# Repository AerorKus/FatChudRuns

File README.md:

# FatChudRuns
Threadmill for the crusty-ass white rat dog Tofu

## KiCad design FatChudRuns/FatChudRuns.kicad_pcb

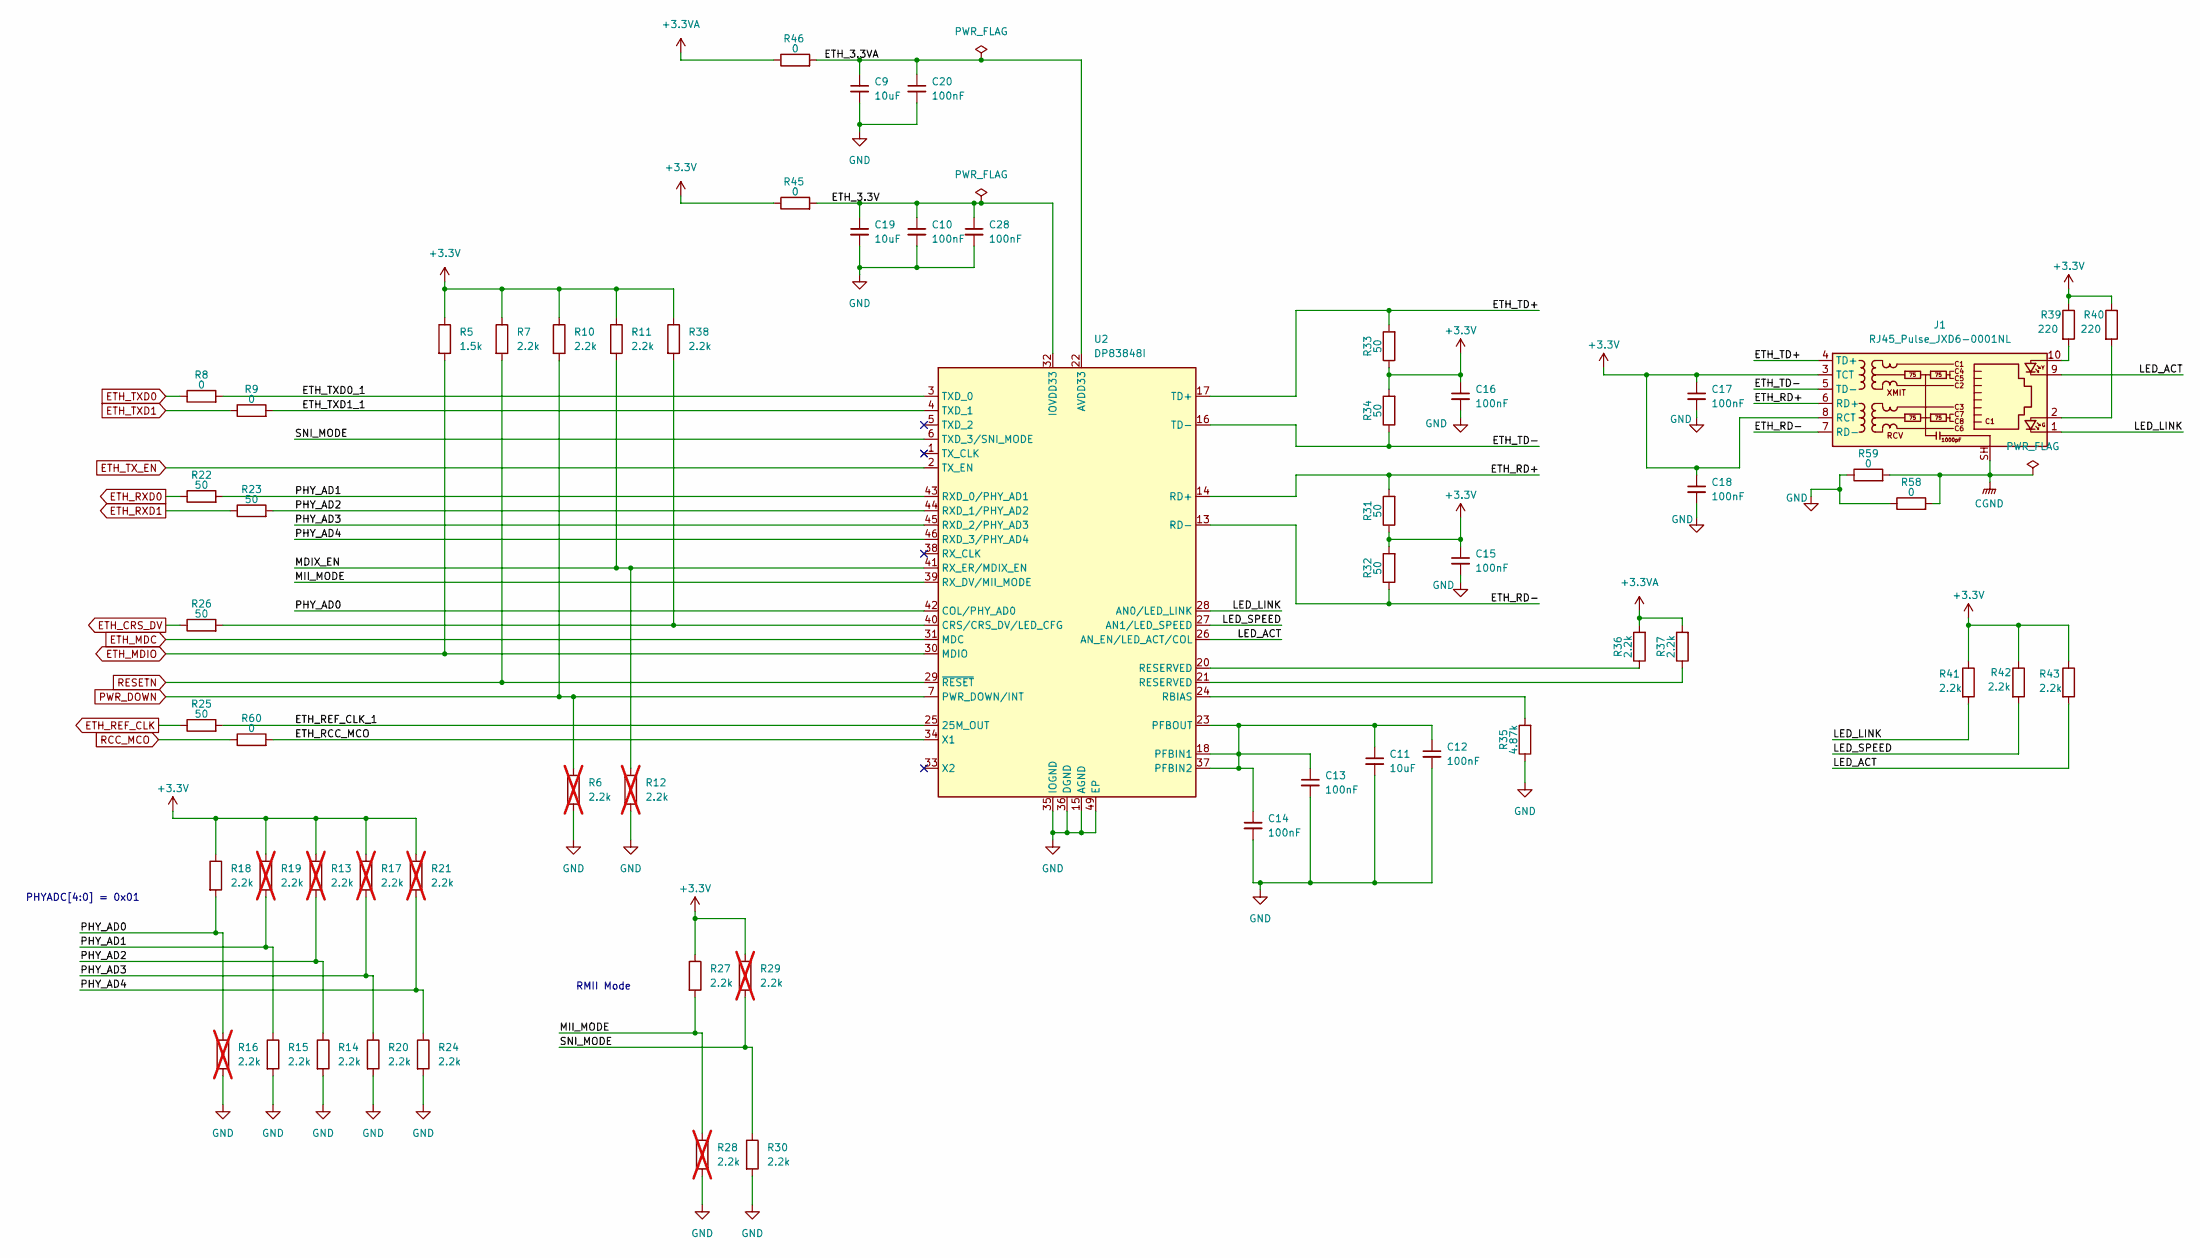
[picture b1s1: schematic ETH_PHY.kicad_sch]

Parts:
C9, C11, C19: 10uF; C_0805_2012Metric; JLCPCB Part # C2167271
C10, C12, C13, C14, C15, C16, C17, C18, C20, C28: 100nF; C_0603_1608Metric; JLCPCB Part # C2181816
J1: RJ45_Pulse_JXD6-0001NL; RJ45_Pulse_JXD6-0001NL_Horizontal; JLCPCB Part # C5359047
R5: 1.5k; R_0603_1608Metric; JLCPCB Part # C114668
R6, R12, R13, R16, R17, R19, R21, R28, R29: 2.2k; R_0603_1608Metric; not fitted
R7, R10, R11, R14, R15, R18, R20, R24, R27, R30, R36, R37, R38, R41, R42, R43: 2.2k; R_0603_1608Metric; JLCPCB Part # C113303
R8, R9, R45, R46, R58, R59, R60: 0; R_0603_1608Metric; JLCPCB Part # C95177
R22, R23, R25, R26, R31, R32, R33, R34: 50; R_0603_1608Metric; JLCPCB Part # C849792
R35: 4.87k; R_0603_1608Metric; JLCPCB Part # C137709
R39, R40: 220; R_0603_1608Metric; JLCPCB Part # C107696
U2: DP83848I; LQFP-48-1EP_7x7mm_P0.5mm_EP3.6x3.6mm_ThermalVias; JLCPCB Part # C12082

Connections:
+3.3V: C15.1, C16.1, C17.1, C18.1, J1.3 (TCT), J1.8 (RCT), R5.1, R7.1, R10.1, R11.1, R13.1, R17.1, R18.1, R19.1, R21.1, R27.1, R29.1, R31.1, R32.2, R33.1, R34.2, R38.1, R39.1, R40.1, R41.1, R42.1, R43.1, R45.1; also elsewhere on the board
+3.3VA: R36.2, R37.2, R46.1; also elsewhere on the board
/ETH_PHY/ETH_3.3V: C10.1, C19.1, C28.1, R45.2, U2.32 (IOVDD33), U2.48 (IOVDD33)
/ETH_PHY/ETH_3.3VA: C9.1, C20.1, R46.2, U2.22 (AVDD33)
/ETH_PHY/ETH_RCC_MCO: R60.2, U2.34 (X1)
/ETH_PHY/ETH_RD+: J1.6 (RD+), R31.2, U2.14 (RD+)
/ETH_PHY/ETH_RD-: J1.7 (RD-), R32.1, U2.13 (RD-)
/ETH_PHY/ETH_REF_CLK_1: R25.2, U2.25 (25M_OUT)
/ETH_PHY/ETH_TD+: J1.4 (TD+), R33.2, U2.17 (TD+)
/ETH_PHY/ETH_TD-: J1.5 (TD-), R34.1, U2.16 (TD-)
/ETH_PHY/ETH_TXD0_1: R8.2, U2.3 (TXD_0)
/ETH_PHY/ETH_TXD1_1: R9.2, U2.4 (TXD_1)
/ETH_PHY/LED_ACT: J1.9, R43.2, U2.26 (AN_EN/LED_ACT/COL)
/ETH_PHY/LED_LINK: J1.1, R41.2, U2.28 (AN0/LED_LINK)
/ETH_PHY/LED_SPEED: R42.2, U2.27 (AN1/LED_SPEED)
/ETH_PHY/MDIX_EN: R11.2, R12.1, U2.41 (RX_ER/MDIX_EN)
/ETH_PHY/MII_MODE: R27.2, R28.1, U2.39 (RX_DV/MII_MODE)
/ETH_PHY/PHY_AD0: R16.1, R18.2, U2.42 (COL/PHY_AD0)
/ETH_PHY/PHY_AD1: R15.1, R19.2, R22.2, U2.43 (RXD_0/PHY_AD1)
/ETH_PHY/PHY_AD2: R13.2, R14.1, R23.2, U2.44 (RXD_1/PHY_AD2)
/ETH_PHY/PHY_AD3: R17.2, R20.1, U2.45 (RXD_2/PHY_AD3)
/ETH_PHY/PHY_AD4: R21.2, R24.1, U2.46 (RXD_3/PHY_AD4)
/ETH_PHY/SNI_MODE: R29.2, R30.1, U2.6 (TXD_3/SNI_MODE)
CGND: J1.SH, R58.2, R59.2
ETH_CRS_DV: R26.1; also elsewhere on the board
ETH_MDC: U2.31 (MDC); also elsewhere on the board
ETH_MDIO: R5.2, U2.30 (MDIO); also elsewhere on the board
ETH_REF_CLK: R25.1; also elsewhere on the board
ETH_RXD0: R22.1; also elsewhere on the board
ETH_RXD1: R23.1; also elsewhere on the board
ETH_TXD0: R8.1; also elsewhere on the board
ETH_TXD1: R9.1; also elsewhere on the board
ETH_TX_EN: U2.2 (TX_EN); also elsewhere on the board
GND: C9.2, C10.2, C11.2, C12.2, C13.2, C14.2, C15.2, C16.2, C17.2, C18.2, C19.2, C20.2, C28.2, R6.2, R12.2, R14.2, R15.2, R16.2, R20.2, R24.2, R28.2, R30.2, R35.1, R58.1, R59.1, U2.15 (AGND), U2.19 (AGND), U2.35 (IOGND), U2.36 (DGND), U2.47 (IOGND), U2.49 (EP); also elsewhere on the board
unnamed: J1.2, R40.2
unnamed: J1.10, R39.2
unnamed: R36.1, U2.20 (RESERVED)
unnamed: R37.1, U2.21 (RESERVED)
unnamed: R26.2, R38.2, U2.40 (CRS/CRS_DV/LED_CFG)
unnamed: C11.1, C12.1, C13.1, C14.1, U2.18 (PFBIN1), U2.23 (PFBOUT), U2.37 (PFBIN2)
unnamed: R35.2, U2.24 (RBIAS)
PWR_DOWN: R6.1, R10.2, U2.7 (PWR_DOWN/INT)
RCC_MCO: R60.1; also elsewhere on the board
RESETN: R7.2, U2.29 (~RESET)

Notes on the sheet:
RMII Mode
PHYADC[4:0] = 0x01

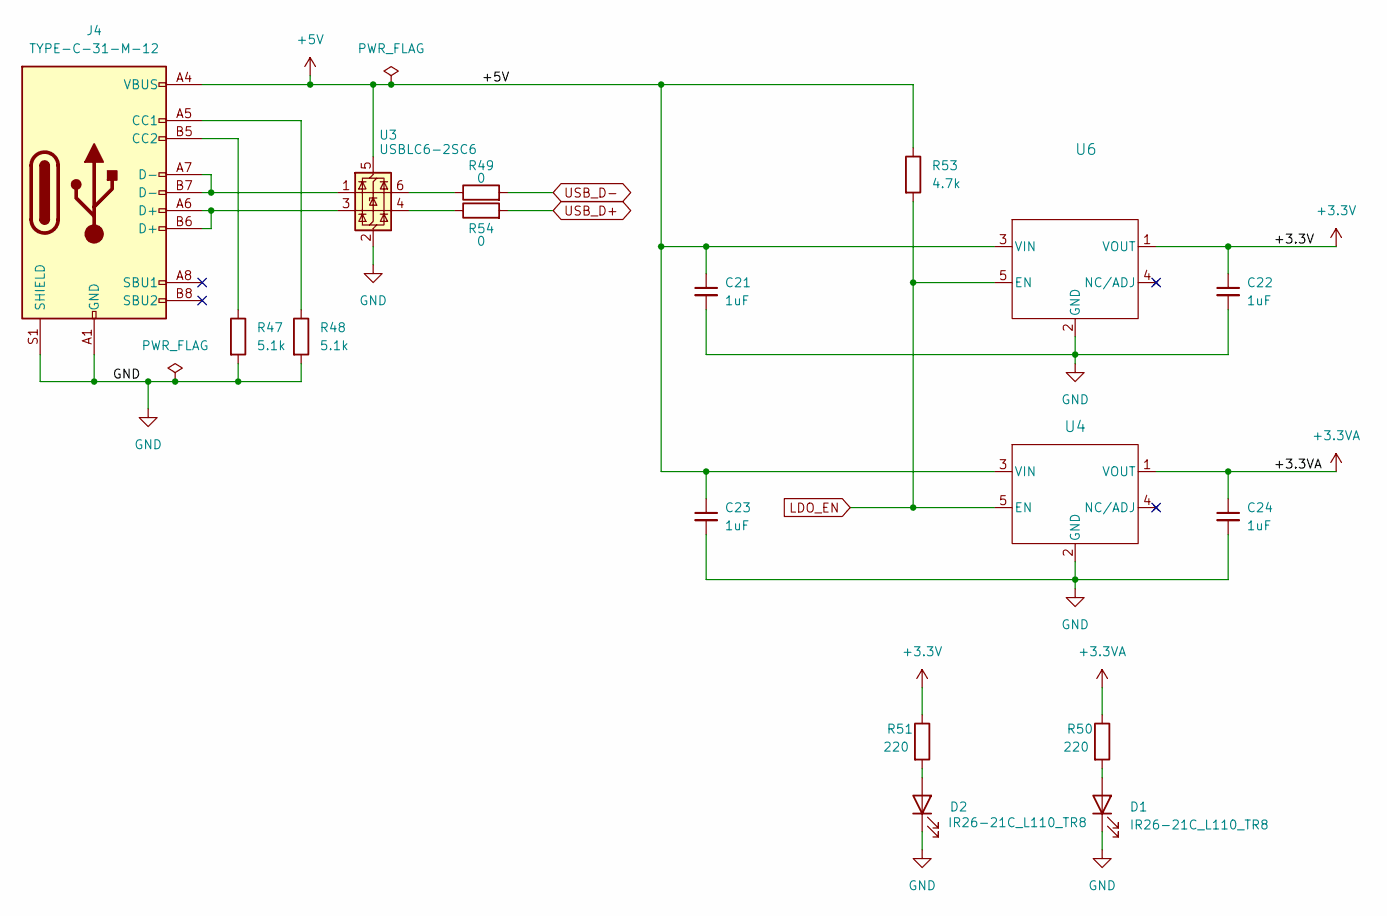
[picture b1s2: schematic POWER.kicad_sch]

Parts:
C21, C22, C23, C24: 1uF; C_0603_1608Metric; JLCPCB Part # C561804
D1, D2: IR26-21C_L110_TR8; LED_1206_3216Metric; JLCPCB Part # C73929
J4: TYPE-C-31-M-12; USB_C_Receptacle_GCT_USB4105-xx-A_16P_TopMnt_Horizontal; JLCPCB Part # C165948
R47, R48: 5.1k; R_0603_1608Metric; JLCPCB Part # C14677
R49, R54: 0; R_0603_1608Metric; JLCPCB Part # C95177
R50, R51: 220; R_0603_1608Metric; JLCPCB Part # C107696
R53: 4.7k; R_0603_1608Metric; JLCPCB Part # C99782
U3: USBLC6-2SC6; SOT-23-6; JLCPCB Part # C7519
U4, U6: ST730M33R; SOT_30M33R_STM; JLCPCB Part # C2846046

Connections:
+3.3V: C22.1, R51.1, U6.1 (VOUT); also elsewhere on the board
+3.3VA: C24.1, R50.1, U4.1 (VOUT); also elsewhere on the board
+5V: C21.1, C23.1, J4.A4 (VBUS), J4.A9 (VBUS), J4.B4 (VBUS), J4.B9 (VBUS), R53.1, U3.5 (VBUS), U4.3 (VIN), U6.3 (VIN)
GND: C21.2, C22.2, C23.2, C24.2, D1.1 (K), D2.1 (K), J4.A1 (GND), J4.A12 (GND), J4.B1 (GND), J4.B12 (GND), J4.S1 (SHIELD), R47.2, R48.2, U3.2 (GND), U4.2 (GND), U6.2 (GND); also elsewhere on the board
LDO_EN: R53.2, U4.5 (EN), U6.5 (EN); also elsewhere on the board
unnamed: D1.2 (A), R50.2
unnamed: D2.2 (A), R51.2
unnamed: J4.A5 (CC1), R48.1
unnamed: J4.B5 (CC2), R47.1
unnamed: J4.A6 (D+), J4.B6 (D+), U3.3 (I/O2)
unnamed: J4.A7 (D-), J4.B7 (D-), U3.1 (I/O1)
unnamed: R49.1, U3.6 (I/O1)
unnamed: R54.1, U3.4 (I/O2)
USB_D+: R54.2; also elsewhere on the board
USB_D-: R49.2; also elsewhere on the board

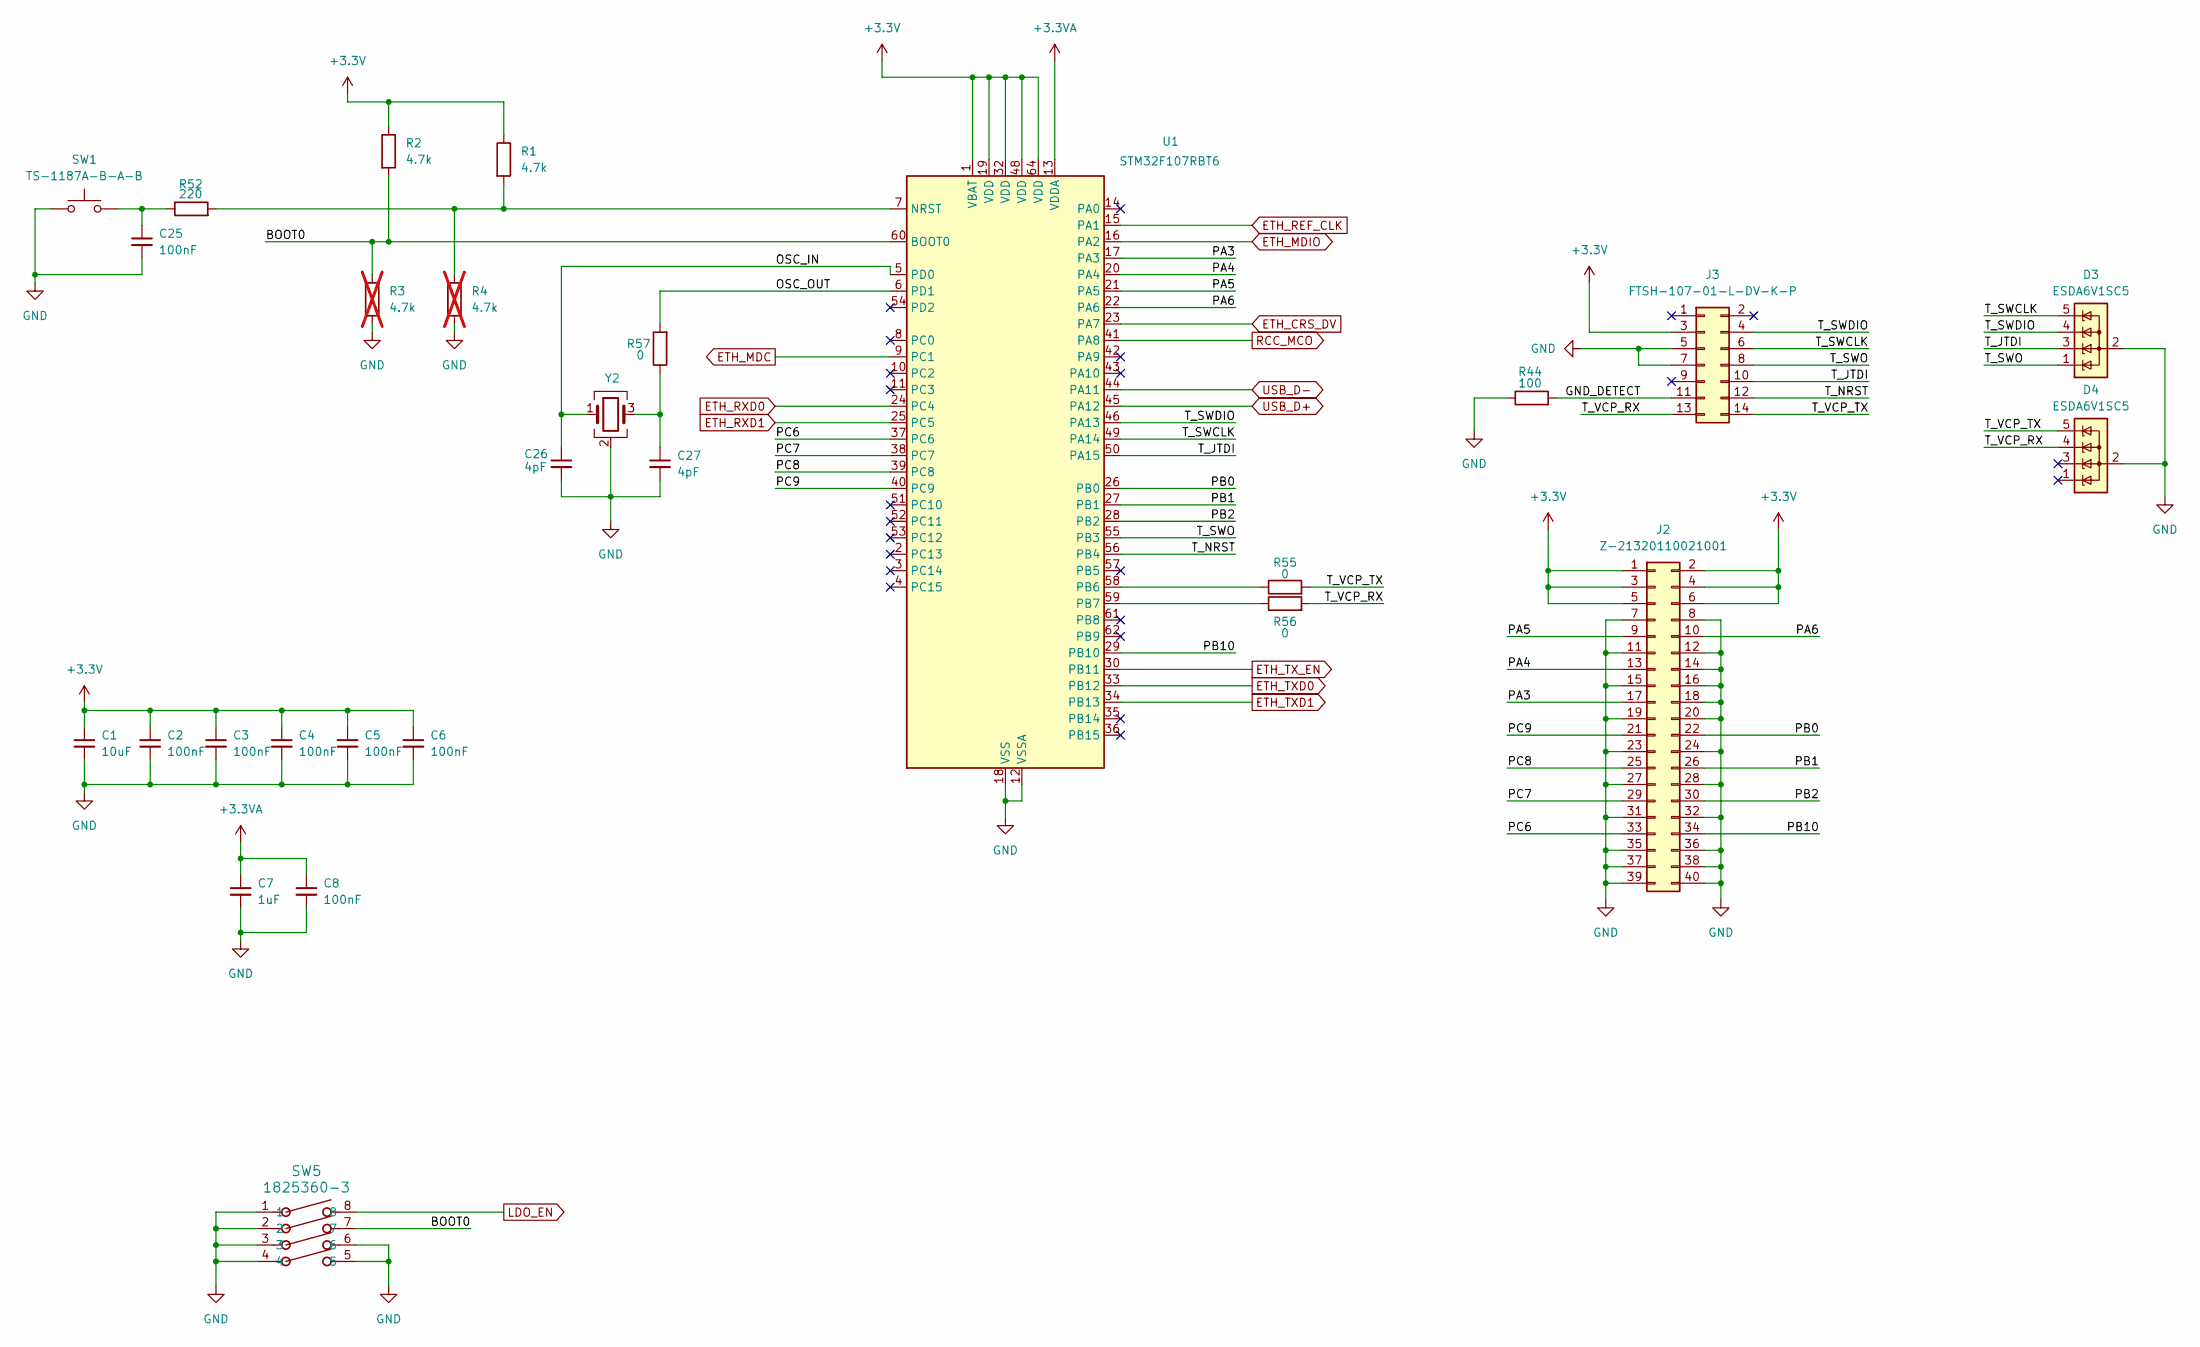
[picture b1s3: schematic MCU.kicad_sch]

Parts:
C1: 10uF; C_0805_2012Metric; JLCPCB Part # C2167271
C2, C3, C4, C5, C6, C8, C25: 100nF; C_0603_1608Metric; JLCPCB Part # C2181816
C7: 1uF; C_0603_1608Metric; JLCPCB Part # C561804
C26, C27: 4pF; C_0603_1608Metric; JLCPCB Part # C309461
D3, D4: ESDA6V1SC5; SOT-23-5; JLCPCB Part # C2935146
J2: Z-21320110021001; PinSocket_2x20_P2.54mm_Vertical; JLCPCB Part # C193453
J3: FTSH-107-01-L-DV-K-P; CON14_2X7_DUK_FTSH_SAI; JLCPCB Part # C5345538
R1, R2: 4.7k; R_0603_1608Metric; JLCPCB Part # C99782
R3, R4: 4.7k; R_0603_1608Metric; not fitted
R44: 100; R_0603_1608Metric; JLCPCB Part # C105588
R52: 220; R_0603_1608Metric; JLCPCB Part # C107696
R55, R56, R57: 0; R_0603_1608Metric; JLCPCB Part # C95177
SW1: TS-1187A-B-A-B; SW_SPST_TL3342; JLCPCB Part # C318884
SW5: 1825360-3; SWDIP8_300X185P100; JLCPCB Part # C574798
U1: STM32F107RBT6; LQFP-64_10x10mm_P0.5mm; JLCPCB Part # C16918
Y2: ABM8G-25.000MHZ-B4Y-T; Crystal_SMD_Abracon_ABM8AIG-4Pin_3.2x2.5mm; JLCPCB Part # C596913

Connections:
+3.3V: C1.1, C2.1, C3.1, C4.1, C5.1, C6.1, J2.1, J2.2, J2.3, J2.4, J2.5, J2.6, J3.3, R1.1, R2.1, U1.1 (VBAT), U1.19 (VDD), U1.32 (VDD), U1.48 (VDD), U1.64 (VDD); also elsewhere on the board
+3.3VA: C7.1, C8.1, U1.13 (VDDA); also elsewhere on the board
/MCU/BOOT0: R2.2, R3.1, SW5.7, U1.60 (BOOT0)
/MCU/GND_DETECT: J3.11, R44.2
/MCU/OSC_IN: C26.1, U1.5 (PD0), Y2.1
/MCU/OSC_OUT: R57.2, U1.6 (PD1)
/MCU/PA3: J2.17, U1.17 (PA3)
/MCU/PA4: J2.13, U1.20 (PA4)
/MCU/PA5: J2.9, U1.21 (PA5)
/MCU/PA6: J2.10, U1.22 (PA6)
/MCU/PB0: J2.22, U1.26 (PB0)
/MCU/PB1: J2.26, U1.27 (PB1)
/MCU/PB2: J2.30, U1.28 (PB2)
/MCU/PB10: J2.34, U1.29 (PB10)
/MCU/PC6: J2.33, U1.37 (PC6)
/MCU/PC7: J2.29, U1.38 (PC7)
/MCU/PC8: J2.25, U1.39 (PC8)
/MCU/PC9: J2.21, U1.40 (PC9)
/MCU/T_JTDI: D3.3 (K), J3.10, U1.50 (PA15)
/MCU/T_NRST: J3.12, U1.56 (PB4)
/MCU/T_SWCLK: D3.5 (K), J3.6, U1.49 (PA14)
/MCU/T_SWDIO: D3.4 (K), J3.4, U1.46 (PA13)
/MCU/T_SWO: D3.1 (K), J3.8, U1.55 (PB3)
/MCU/T_VCP_RX: D4.4 (K), J3.13, R56.2
/MCU/T_VCP_TX: D4.5 (K), J3.14, R55.2
ETH_CRS_DV: U1.23 (PA7); also elsewhere on the board
ETH_MDC: U1.9 (PC1); also elsewhere on the board
ETH_MDIO: U1.16 (PA2); also elsewhere on the board
ETH_REF_CLK: U1.15 (PA1); also elsewhere on the board
ETH_RXD0: U1.24 (PC4); also elsewhere on the board
ETH_RXD1: U1.25 (PC5); also elsewhere on the board
ETH_TXD0: U1.33 (PB12); also elsewhere on the board
ETH_TXD1: U1.34 (PB13); also elsewhere on the board
ETH_TX_EN: U1.30 (PB11); also elsewhere on the board
GND: C1.2, C2.2, C3.2, C4.2, C5.2, C6.2, C7.2, C8.2, C25.2, C26.2, C27.2, D3.2 (A), D4.2 (A), J2.7, J2.8, J2.11, J2.12, J2.14, J2.15, J2.16, J2.18, J2.19, J2.20, J2.23, J2.24, J2.27, J2.28, J2.31, J2.32, J2.35, J2.36, J2.37, J2.38, J2.39, J2.40, J3.5, J3.7, R3.2, R4.2, R44.1, SW1.1, SW5.1, SW5.2, SW5.3, SW5.4, SW5.5, SW5.6, U1.12 (VSSA), U1.18 (VSS), U1.31 (VSS), U1.47 (VSS), U1.63 (VSS), Y2.2 (G), Y2.4 (G); also elsewhere on the board
LDO_EN: SW5.8; also elsewhere on the board
unnamed: C25.1, R52.1, SW1.2
unnamed: C27.1, R57.1, Y2.3
unnamed: R1.2, R4.1, R52.2, U1.7 (NRST)
unnamed: R55.1, U1.58 (PB6)
unnamed: R56.1, U1.59 (PB7)
RCC_MCO: U1.41 (PA8); also elsewhere on the board
USB_D+: U1.45 (PA12); also elsewhere on the board
USB_D-: U1.44 (PA11); also elsewhere on the board

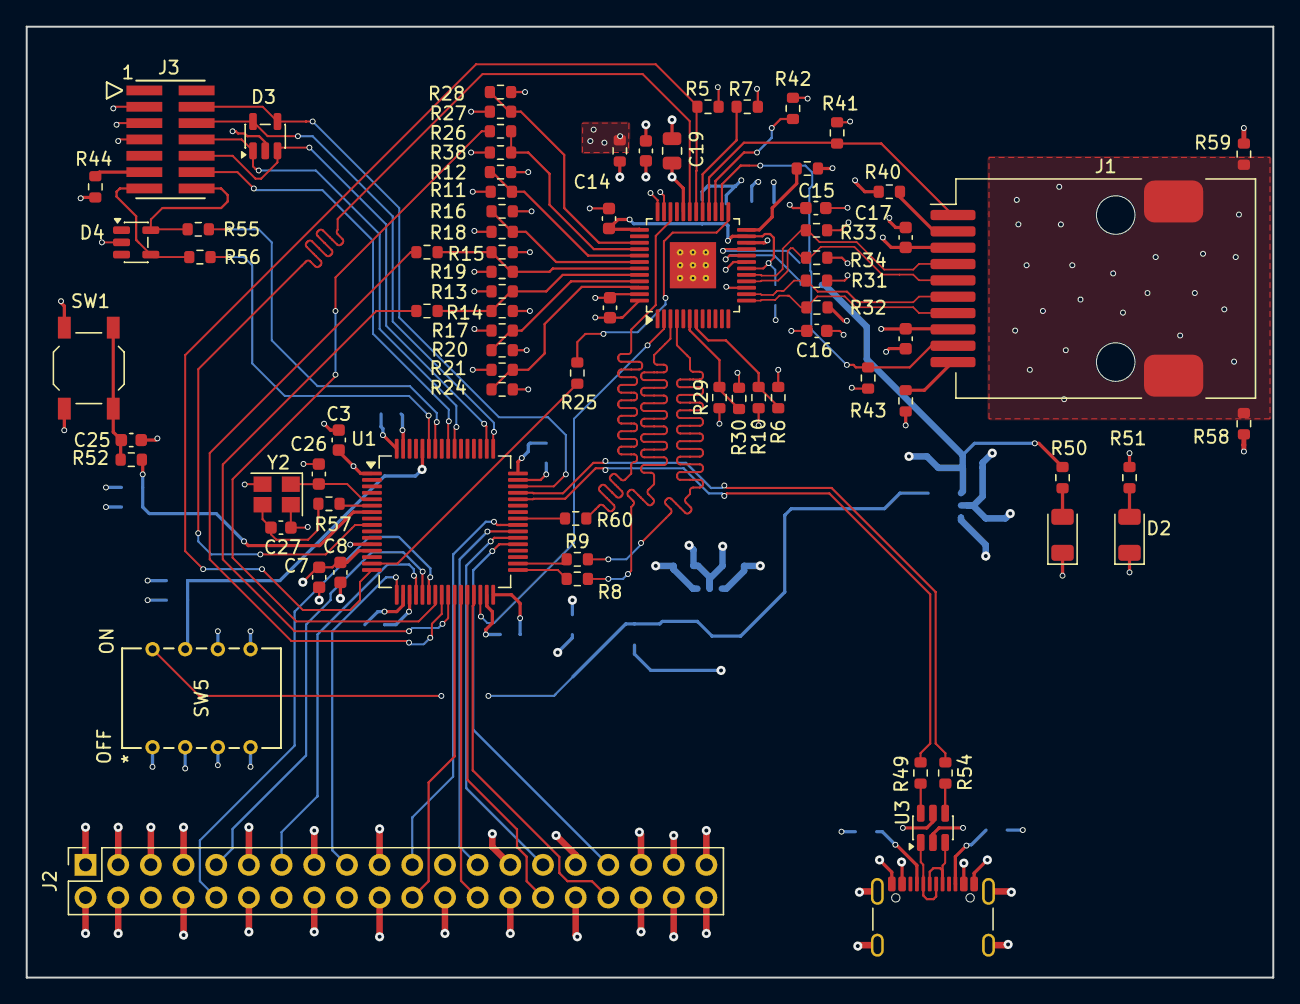
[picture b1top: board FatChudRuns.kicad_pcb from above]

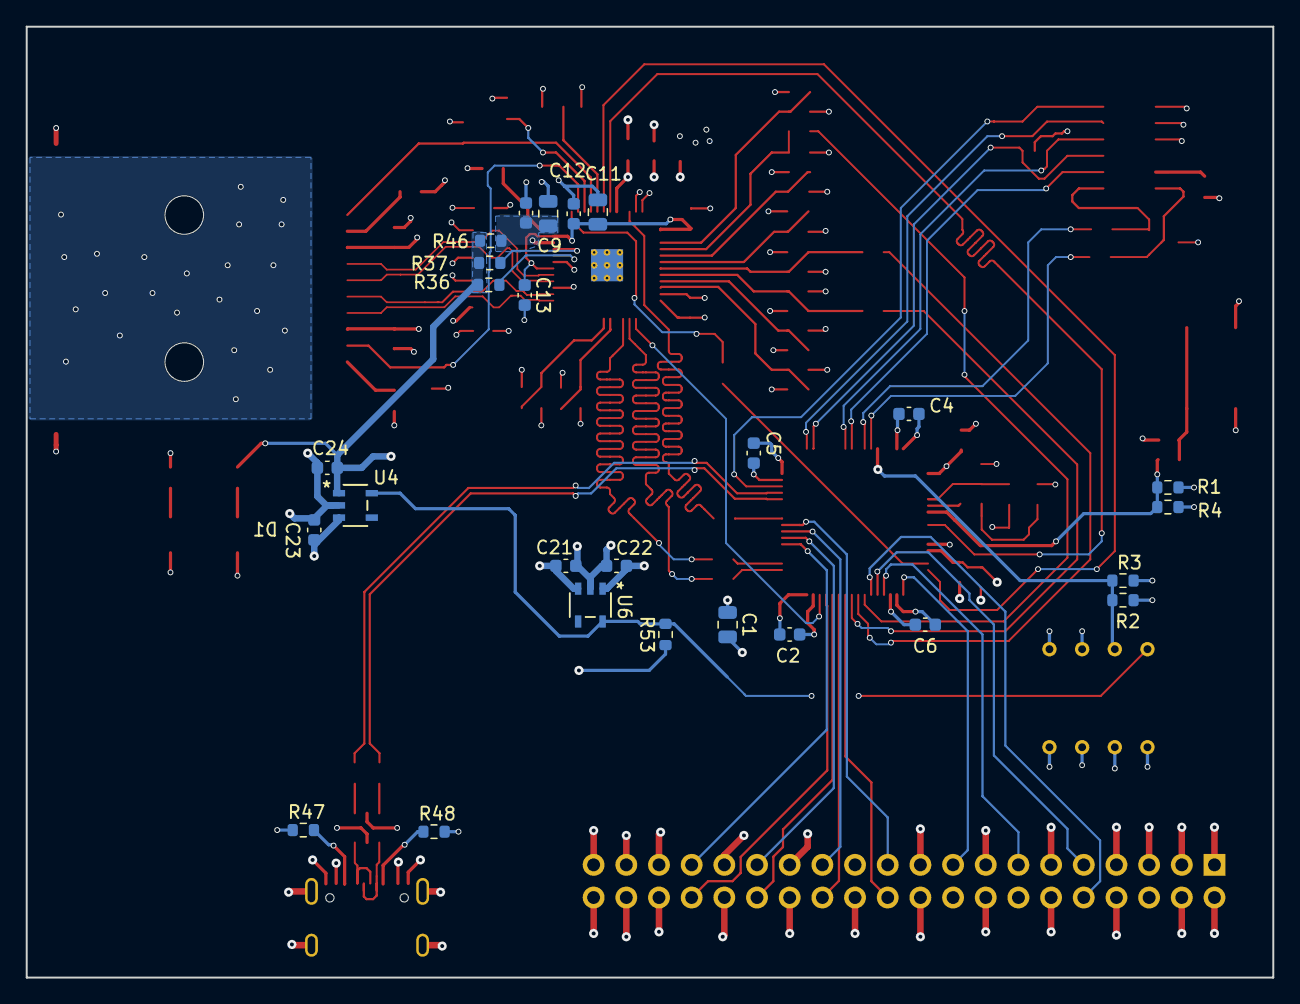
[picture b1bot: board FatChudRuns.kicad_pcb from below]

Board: 4 copper layers, 96.9 x 73.9 mm, 104 parts (26 on the bottom side), 84 nets.

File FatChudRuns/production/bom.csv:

Designator,Footprint,Quantity,Value,LCSC Part #
"C1, C11, C19, C9",0805,4,10uF,C2167271
"C10, C12, C13, C14, C15, C16, C17, C18, C2, C20, C25, C28, C3, C4, C5, C6, C8",0603,17,100nF,C2181816
"C21, C22, C23, C24, C7",0603,5,1uF,C561804
"C26, C27",0603,2,4pF,C309461
"D1, D2",1206,2,IR26-21C_L110_TR8,C73929
"D3, D4",SOT-23-5,2,ESDA6V1SC5,C2935146
J1,RJ45_Pulse_JXD6-0001NL_Horizontal,1,RJ45_Pulse_JXD6-0001NL,C5359047
J2,PinSocket_2x20_P2.54mm_Vertical,1,2.54mm 2*20P直排针,C50980
J3,CON14_2X7_DUK_FTSH_SAI,1,FTSH-107-01-L-DV-K-P,C5345538
J4,USB_C_Receptacle_GCT_USB4105-xx-A_16P_TopMnt_Horizontal,1,TYPE-C-31-M-12,C165948
"R1, R2, R53",0603,3,4.7k,C99782
"R10, R11, R14, R15, R18, R20, R24, R27, R30, R36, R37, R38, R41, R42, R43, R7",0603,16,2.2k,C113303
"R22, R23, R25, R26, R31, R32, R33, R34",0603,8,50,C849792
R35,0603,1,4.87k,C137709
"R39, R40, R50, R51, R52",0603,5,220,C107696
R44,0603,1,100,C105588
"R45, R46, R49, R54, R55, R56, R57, R58, R59, R60, R8, R9",0603,12,0,C95177
"R47, R48",0603,2,5.1k,C14677
R5,0603,1,1.5k,C114668
SW1,SW_SPST_TL3342,1,TS-1187A-B-A-B,C318884
SW5,SWDIP8_300X185P100,1,1825360-3,C574798
U1,LQFP-64_10x10mm_P0.5mm,1,STM32F107RBT6,C16918
U2,LQFP-48-1EP_7x7mm_P0.5mm_EP3.6x3.6mm_ThermalVias,1,DP83848I,C12082
U3,SOT-23-6,1,USBLC6-2SC6,C7519
"U4, U6",SOT_30M33R_STM,2,ST730M33R,C2846046
Y2,Crystal_SMD_Abracon_ABM8AIG-4Pin_3.2x2.5mm,1,ABM8G-25.000MHZ-B4Y-T,C596913

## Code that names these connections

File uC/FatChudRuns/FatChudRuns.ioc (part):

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Mcu.Name=STM32F107R(B-C)Tx
Mcu.Package=LQFP64
Mcu.UserName=STM32F107RBTx
PA1.Mode=RMII
PA1.Signal=ETH_REF_CLK
PA10.Mode=Asynchronous
PA10.Signal=USART1_RX
PA11.Mode=Device_Only
PA11.Signal=USB_OTG_FS_DM
PA12.Mode=Device_Only
PA12.Signal=USB_OTG_FS_DP
PA13.Mode=JTAG_5_pins
PA13.Signal=SYS_JTMS-SWDIO
PA14.Mode=JTAG_5_pins
PA14.Signal=SYS_JTCK-SWCLK
PA15.Mode=JTAG_5_pins
PA15.Signal=SYS_JTDI
PA2.Mode=RMII
PA2.Signal=ETH_MDIO
PA7.Mode=RMII
PA7.Signal=ETH_CRS_DV
PA8.Mode=Clock-out
PA8.Signal=RCC_MCO
PA9.Mode=Asynchronous
PA9.Signal=USART1_TX
PB11.Mode=RMII
PB11.Signal=ETH_TX_EN
PB12.Mode=RMII
PB12.Signal=ETH_TXD0
PB13.Mode=RMII
PB13.Signal=ETH_TXD1
PB3.Mode=JTAG_5_pins
PB3.Signal=SYS_JTDO
PB4.Mode=JTAG_5_pins
PB4.Signal=SYS_NJTRST
PC1.Mode=RMII
PC1.Signal=ETH_MDC
PC4.Mode=RMII
PC4.Signal=ETH_RXD0
PC5.Mode=RMII
PC5.Signal=ETH_RXD1
PC6.Signal=S_TIM3_CH1
PC7.Signal=S_TIM3_CH2
PC8.Signal=S_TIM3_CH3
PC9.Signal=S_TIM3_CH4
PD0-OSC_IN.Mode=HSE-External-Oscillator
PD0-OSC_IN.Signal=RCC_OSC_IN
PD1-OSC_OUT.Mode=HSE-External-Oscillator
PD1-OSC_OUT.Signal=RCC_OSC_OUT
RCC.HSEDivPLL=RCC_HSE_PREDIV_DIV5
RCC.HSE_VALUE=25000000
RCC.SYSCLKFreq_VALUE=72000000
RCC.SYSCLKSource=RCC_SYSCLKSOURCE_PLLCLK
board=custom

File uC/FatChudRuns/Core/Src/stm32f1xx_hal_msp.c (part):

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    __HAL_RCC_GPIOA_CLK_ENABLE();
    /**ADC2 GPIO Configuration
    PA0-WKUP     ------> ADC2_IN0
    PA3     ------> ADC2_IN3
    */
    GPIO_InitStruct.Pin = GPIO_PIN_0|GPIO_PIN_3;
    GPIO_InitStruct.Mode = GPIO_MODE_ANALOG;
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
    /**ADC2 GPIO Configuration
    PA0-WKUP     ------> ADC2_IN0
    PA3     ------> ADC2_IN3
    */
    HAL_GPIO_DeInit(GPIOA, GPIO_PIN_0|GPIO_PIN_3);

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
    __HAL_RCC_GPIOA_CLK_ENABLE();
    /**DAC GPIO Configuration
    PA4     ------> DAC_OUT1
    PA5     ------> DAC_OUT2
    */
    GPIO_InitStruct.Pin = GPIO_PIN_4|GPIO_PIN_5;
    GPIO_InitStruct.Mode = GPIO_MODE_ANALOG;
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    __HAL_RCC_DAC_CLK_DISABLE();

    /**DAC GPIO Configuration
    PA4     ------> DAC_OUT1
    PA5     ------> DAC_OUT2
    */
    HAL_GPIO_DeInit(GPIOA, GPIO_PIN_4|GPIO_PIN_5);

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    __HAL_RCC_GPIOA_CLK_ENABLE();
    __HAL_RCC_GPIOB_CLK_ENABLE();
    /**ETH GPIO Configuration
    PC1     ------> ETH_MDC
    PA1     ------> ETH_REF_CLK
    PA2     ------> ETH_MDIO
    PA7     ------> ETH_CRS_DV
    PC4     ------> ETH_RXD0
    PC5     ------> ETH_RXD1
    PB11     ------> ETH_TX_EN
    PB12     ------> ETH_TXD0
    PB13     ------> ETH_TXD1
    */
    GPIO_InitStruct.Pin = GPIO_PIN_1;
    GPIO_InitStruct.Mode = GPIO_MODE_AF_PP;
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    __HAL_RCC_ETH_CLK_DISABLE();

    /**ETH GPIO Configuration
    PC1     ------> ETH_MDC
    PA1     ------> ETH_REF_CLK
    PA2     ------> ETH_MDIO
    PA7     ------> ETH_CRS_DV
    PC4     ------> ETH_RXD0
    PC5     ------> ETH_RXD1
    PB11     ------> ETH_TX_EN
    PB12     ------> ETH_TXD0
    PB13     ------> ETH_TXD1
    */
    HAL_GPIO_DeInit(GPIOC, GPIO_PIN_1|GPIO_PIN_4|GPIO_PIN_5);

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
    __HAL_RCC_GPIOB_CLK_ENABLE();
    /**TIM3 GPIO Configuration
    PB0     ------> TIM3_CH3
    PB1     ------> TIM3_CH4
    PB4     ------> TIM3_CH1
    PB5     ------> TIM3_CH2
    */
    GPIO_InitStruct.Pin = GPIO_PIN_0|GPIO_PIN_1|GPIO_PIN_4|GPIO_PIN_5;
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
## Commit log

2026-02-07 updated stm32 firmware for pin selection, added pcb guidelines pdf
2026-02-10 added switch and dip switch for mcu, decoup caps. new sheets for power and eth phy
2026-02-11 connected phy to uC and added strapping options
2026-02-12 added filters and decoup caps, updated series term
2026-02-19 selected rj45 w/ mag, fixed filtering for power, added snippets of layout recs
2026-02-23 connected rj45 and leds and led strapping resistors
2026-03-01 added connectors for gpio and jtag, need to verify orientation
2026-03-02 added debugger and nucleo ref sch
2026-03-03 connected remaining gpio pins to connector, added kicad power pins instead of net names
2026-03-04 add usb c power circuitry, added led for power indication, increased resistance of ethernet leds light to 220ohms
2026-03-04 cleaned up ref folder, added ldo datasheet
2026-03-07 sorted out erc errors and warning, connected tvs diodes to jtag
2026-03-09 added caps and diode footprints, all caps now non-polarized ceramic caps
2026-03-14 added footprint for switches and button - ready for layout
2026-03-20 setup stackup and constraints
2026-03-22 added 4pF caps and Rext to XTAL, initial placement of PCB, added board outline and gnd plane
2026-03-23 routed ETH MDI and magnetics portion with chassis ground. added 0ohm resistors to connect gnd and cgnd
2026-03-24 added one more decoup cap for eth phy (another power pin), routed decoup caps, routed phy filter resistors
2026-03-29 routed phy usb and clock
2026-03-31 routed jtag, ldo, switch, reset button, and decoupling caps. only need GPIO signals
2026-04-01 finished initial layout, removed some gpio pins and reorganized them
2026-04-01 updated constraints, parsed through most drc
2026-04-03 cleared the rest of the drc - layout complete
2026-04-03 created gerbers, need to fix dfm
2026-04-10 updated 3d model footprint for Rj45 (created new library)
2026-04-10 updated 10uF to 0805, completed BOM, sent to fab

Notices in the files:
uC/FatChudRuns/Core/Src/stm32f1xx_hal_msp.c:
Copyright (c) 2026 STMicroelectronics.
All rights reserved.
This software is licensed under terms that can be found in the LICENSE file
